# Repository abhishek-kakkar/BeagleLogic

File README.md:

===========

NEW: The BeagleLogic cape is here! To get more information please click [here]
(https://github.com/abhishek-kakkar/BeagleLogic/wiki/The-BeagleLogic-Cape).

Bootstrapped as a Google Summer of Code 2014 Project with BeagleBoard.org.

For detailed information and usage guide refer to
[the project wiki](https://github.com/abhishek-kakkar/BeagleLogic/wiki)

BeagleLogic realizes a logic analyzer on the BeagleBone / the BeagleBone Black using
the Programmable Real-Time units and matching firmware and Linux kernel modules on the
BeagleBone Black.

The software should also work on the BeagleBone White, but with limited memory support
(only 256 MB instead of 512 MB)

BeagleLogic can also be used in conjunction with the sigrok projects to capture and process
the data on the BeagleBone itself. The libsigrok bindings for BeagleLogic have been accepted
into the upstream libsigrok repository.

Directories:

* firmware: PRU Firmware
* kernel: Device Tree overlay source and kernel module source and Makefile.
**The default BeagleBone kernel v4.9.31-ti-r41 and above ship with BeagleLogic support.
You can verify it using the command** ```modinfo beaglelogic```
* server: Node.JS backend and static file server for the web interface
* cape: The cape design files (KiCAD schematic and PCB file only. Production Gerbers are available separately.)
* webapp: A minimal web client for BeagleLogic. Uses sigrok-cli internally for data
acquisition
* testapp: A simple test application that shows how to use the userspace API of BeagleLogic
and benchmarks memory copy speeds.
 
Selected binaries and archives related to the project may be downloaded from
[this link](http://goo.gl/770FTZ). Refer to the wiki for more information 
regarding the use of the archives and the binaries.

License
--------

 * **PRU firmware & Device tree overlay** : GPLv2
 * **Kernel Module**: GPLv2
 * **sigrok bindings**: GPLv3+
 * **Web interface** [/beaglelogic-server and /webapp]: MIT
 * **Cape** : CERN Open Hardware License
 * **Logo** : [Creative Commons Attribution-ShareAlike 4.0 International (CC-BY-SA-4.0)]
(http://creativecommons.org/licenses/by-sa/4.0/)

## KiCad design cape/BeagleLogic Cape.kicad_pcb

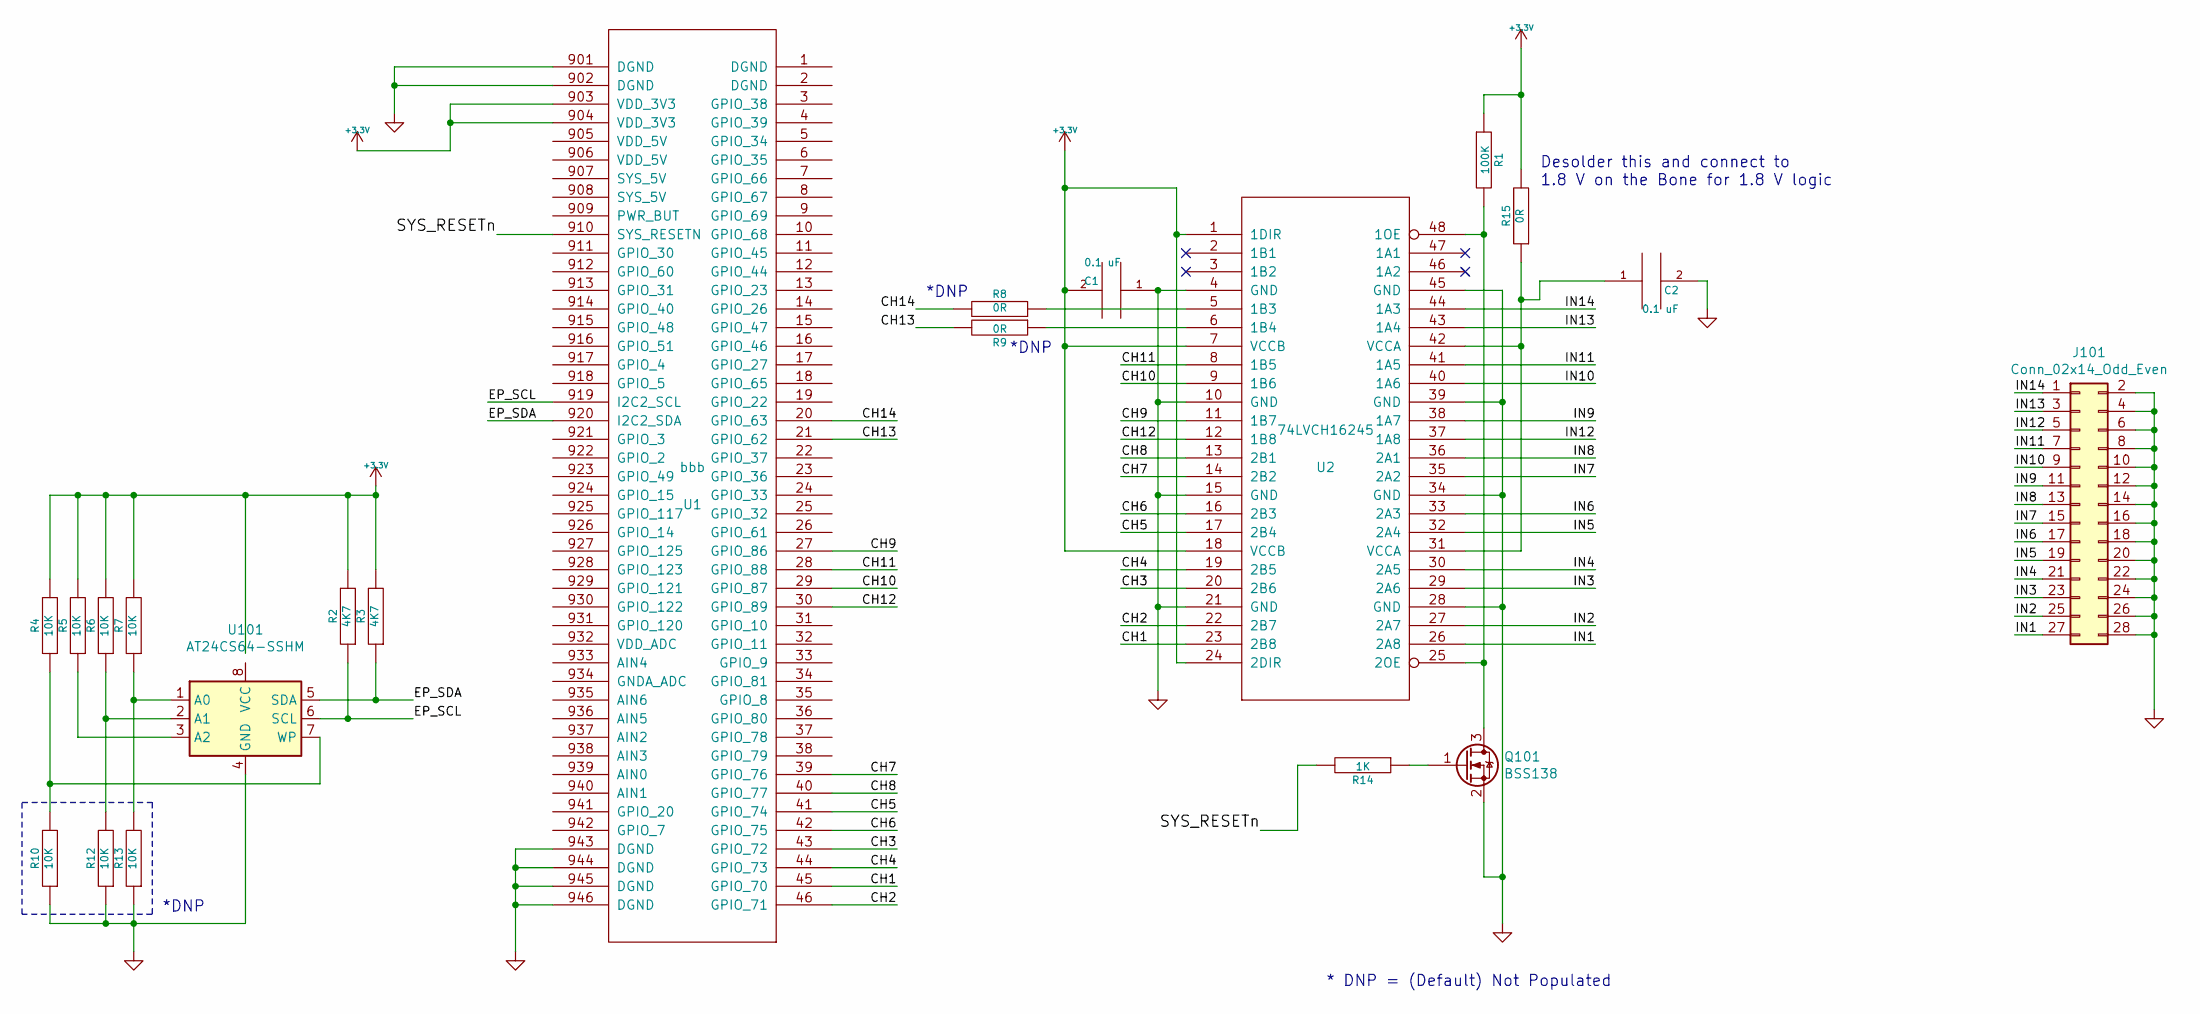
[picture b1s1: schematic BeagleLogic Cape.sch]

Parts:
C1, C2: 0.1 uF; SMD-0603
J101: Conn_02x14_Odd_Even; Pin_Header_Angled_2x14
Q101: BSS138; SOT-23_Handsoldering
R1: 100K; R_0603
R2, R3: 4K7; R_0603
R4, R5, R6, R7, R10, R12, R13: 10K; R_0603
R8, R9, R15: 0R; R_0603
R14: 1K; R_0603
U1: bbb; BBB
U2: 74LVCH16245; TSSOP-48_6.1x12.5mm_Pitch0.5mm
U101: AT24CS64-SSHM; SOIC-8-N

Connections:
+3V3: C1.2, R1.1, R2.2, R3.2, R4.2, R5.2, R6.2, R7.2, R15.2, U1.903 (VDD_3V3), U1.904 (VDD_3V3), U2.1 (1DIR), U2.7 (VCCB), U2.18 (VCCB), U2.24 (2DIR)
/CH1: U1.45 (GPIO_70), U2.23 (2B8)
/CH2: U1.46 (GPIO_71), U2.22 (2B7)
/CH3: U1.43 (GPIO_72), U2.20 (2B6)
/CH4: U1.44 (GPIO_73), U2.19 (2B5)
/CH5: U1.41 (GPIO_74), U2.17 (2B4)
/CH6: U1.42 (GPIO_75), U2.16 (2B3)
/CH7: U1.39 (GPIO_76), U2.14 (2B2)
/CH8: U1.40 (GPIO_77), U2.13 (2B1)
/CH9: U1.27 (GPIO_86), U2.11 (1B7)
/CH10: U1.29 (GPIO_87), U2.9 (1B6)
/CH11: U1.28 (GPIO_88), U2.8 (1B5)
/CH12: U1.30 (GPIO_89), U2.12 (1B8)
/CH13: R9.2, U1.21 (GPIO_62)
/CH14: R8.2, U1.20 (GPIO_63)
/EP_SCL: R2.1, U1.919 (I2C2_SCL), U101.6 (SCL)
/EP_SDA: R3.1, U1.920 (I2C2_SDA), U101.5 (SDA)
/IN1: J101.27, U2.26 (2A8)
/IN2: J101.25, U2.27 (2A7)
/IN3: J101.23, U2.29 (2A6)
/IN4: J101.21, U2.30 (2A5)
/IN5: J101.19, U2.32 (2A4)
/IN6: J101.17, U2.33 (2A3)
/IN7: J101.15, U2.35 (2A2)
/IN8: J101.13, U2.36 (2A1)
/IN9: J101.11, U2.38 (1A7)
/IN10: J101.9, U2.40 (1A6)
/IN11: J101.7, U2.41 (1A5)
/IN12: J101.5, U2.37 (1A8)
/IN13: J101.3, U2.43 (1A4)
/IN14: J101.1, U2.44 (1A3)
/SYS_RESETn: R14.2, U1.910 (SYS_RESETN)
GND: C1.1, C2.2, J101.2, J101.4, J101.6, J101.8, J101.10, J101.12, J101.14, J101.16, J101.18, J101.20, J101.22, J101.24, J101.26, J101.28, Q101.2 (S), R10.1, R12.1, R13.1, U1.901 (DGND), U1.902 (DGND), U1.943 (DGND), U1.944 (DGND), U1.945 (DGND), U1.946 (DGND), U2.4 (GND), U2.10 (GND), U2.15 (GND), U2.21 (GND), U2.28 (GND), U2.34 (GND), U2.39 (GND), U2.45 (GND), U101.4 (GND)
unnamed: C2.1, R15.1, U2.31 (VCCA), U2.42 (VCCA)
unnamed: Q101.1 (G), R14.1
unnamed: Q101.3 (D), R1.2, U2.25 (2OE), U2.48 (1OE)
unnamed: R5.1, U101.3 (A2)
unnamed: R8.1, U2.5 (1B3)
unnamed: R9.1, U2.6 (1B4)
unnamed: R4.1, R10.2, U101.7 (WP)
unnamed: R6.1, R12.2, U101.2 (A1)
unnamed: R7.1, R13.2, U101.1 (A0)

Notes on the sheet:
*DNP
* DNP = (Default) Not Populated
Desolder this and connect to 1.8 V on the Bone for 1.8 V logic

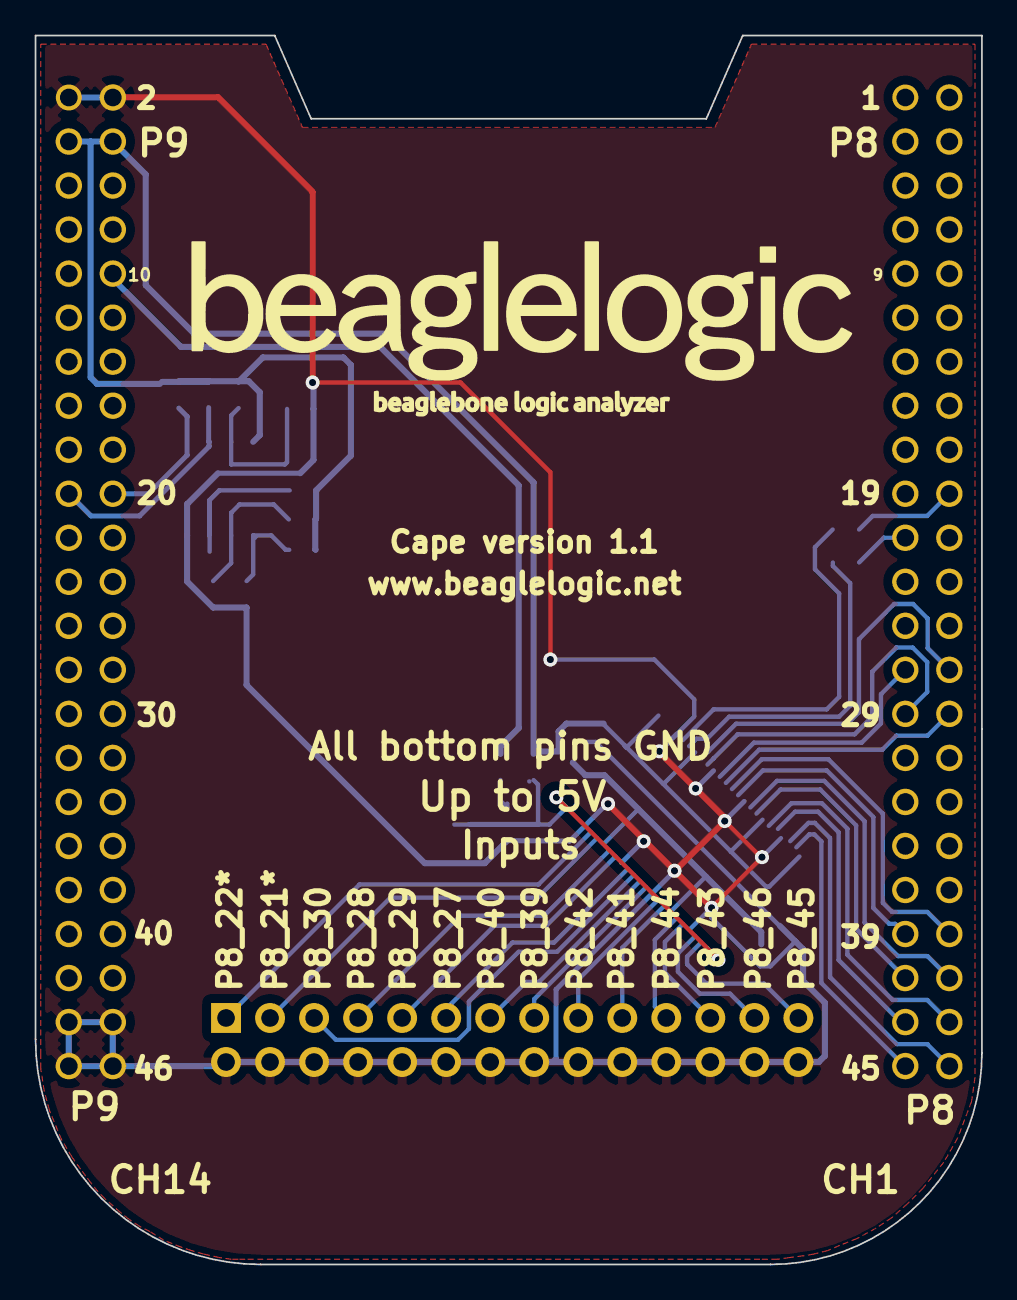
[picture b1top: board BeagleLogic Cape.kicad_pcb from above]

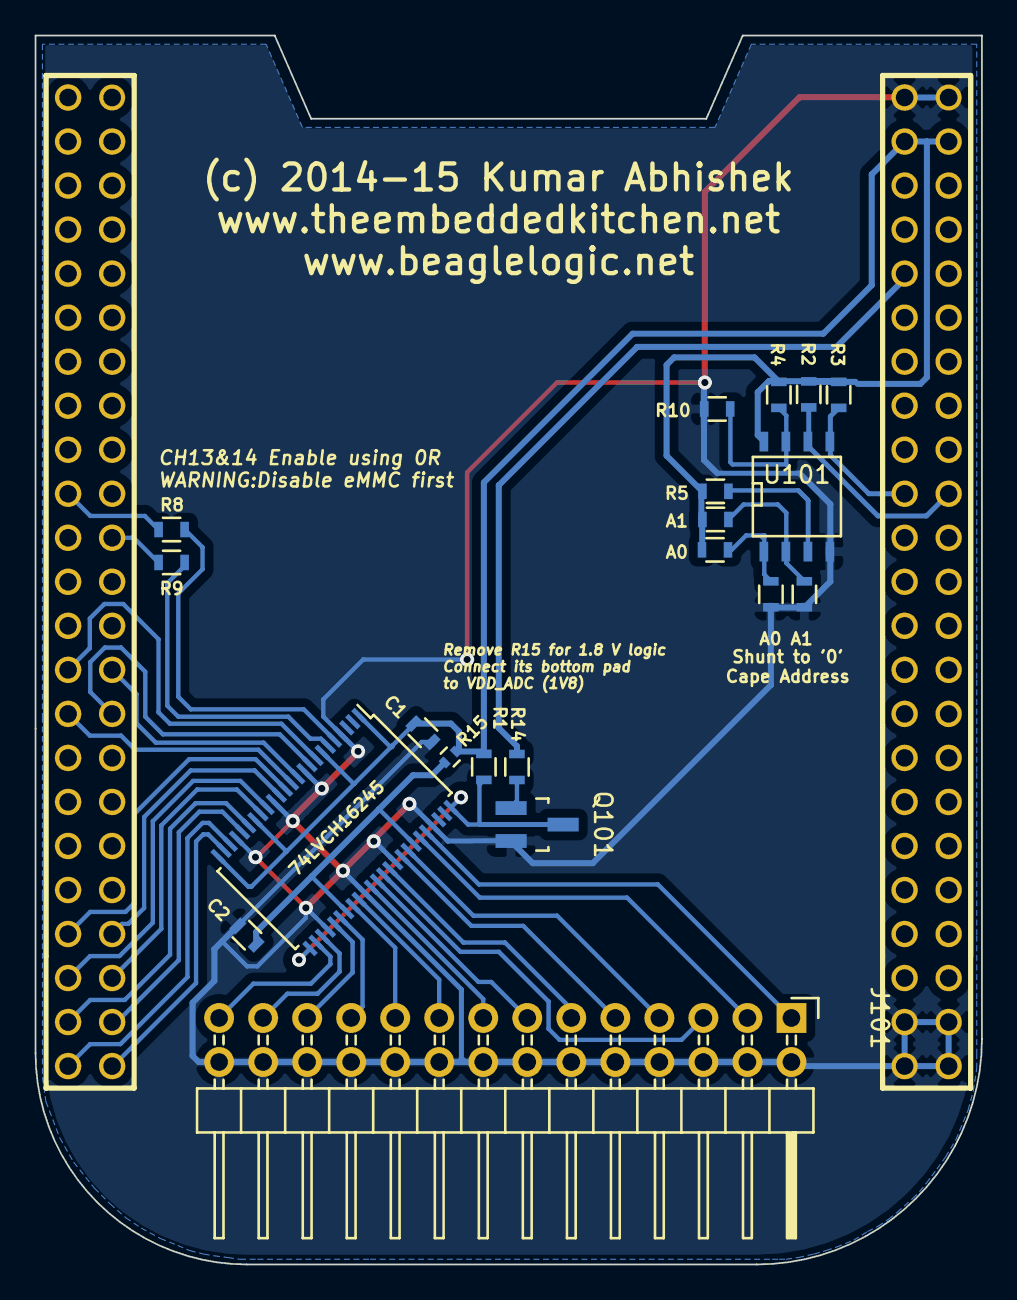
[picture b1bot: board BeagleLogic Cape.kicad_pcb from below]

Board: 2 copper layers, 54.6 x 70.9 mm, 21 parts (21 on the bottom side), 42 nets.

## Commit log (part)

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2014-05-13 .gitignore update
2014-05-13 README.md update
2014-05-20 More PRU stuff
2014-05-21 Broadside transfers working: First implementation
    Next stop: Circular transfers
2014-05-23 [pru1fw.asm]: Shift sample bank from R4-R11 to R14-R21 (possibly till R29)
2014-06-05 Add BeagleLogic device tree file and compiled overlay
2014-06-05 Add fork of pru_rproc driver as kernel module
    pru_rproc_bl.c
    Includes Matt Ranostay's lighting example
2014-06-05 Fix compile issues arising from modularization of pru_rproc
2014-06-05 [WIP] BeagleLogic PRU Firmware port to CLPRU2.0.0
    With Makefile and linker scripts.
2014-06-09 BeagleLogic kernel driver: Update path in Makefile
2014-06-09 [PRU0 FW] Port data transfer core from PASM
2014-06-09 [PRU1 FW] Shift sample capture from R13-R21 to R21-R29
2014-06-11 Use kmalloc and cache management instead of dma_alloc_coherent
2014-06-15 Kernel Module migration stage1:Cleanup beaglelogic.c
2014-06-16 Kernel module migration: Cleanup pru_rproc_bl.c
    The code in pru_rproc_bl.c is now fully independent of
    the beaglelogic module.
    Add link functions to beaglelogic module
2014-06-18 Final touches to the glue code
2014-06-20 [PRU0FW Core] Cleanup & Enable halt-on-hostrequest
    The PRU firmware now aborts sampling and resets after
    receiving an ARM->host1 interrupt
2014-06-20 [PRU1FW] Unified firmware for all sample configs
    The delay loop values are written into PRU1 registers by
    PRU0 and are used to jump to the appropriate (8-bit or
    16-bit sample) sample loop.
    Supported sample rates: (100 / n) MHz
    Sample units: 8 bits or 16-bits
2014-06-20 Kernel Driver: Add idx parameter to pru_start
    For future use, single-PRU firmware
2014-06-20 Kernel Driver: Assorted Cleanups & Fixes
    TODO:
    * Implement write overrun checks
    * Device tree parameter reads
2014-06-22 Kernel Driver: Add version information & load-time alloc unit setting
2014-06-22 Kernel Driver: Add loading initial configuration from the device tree
2014-06-22 Kernel Driver: Fix behaviour of sysfs state attribute
2014-06-22 Kernel Driver: cleanup core data structures
2014-06-22 Kernel Driver: implement overrun detection
    This allows the driver to flag a warning log & lasterror when a new
    buffer comes in before the previous one has been copied out completely.
    Also modify IRQ to prevent false buffer overrun on the last buffer
    readout.
2014-06-22 Kernel Driver: more cleanups
    Change loglevel of select messages to dev_dbg
2014-06-22 DTS: Rename to BB-BEAGLELOGIC-00A0.dts
2014-06-22 PRU Firmware: Add install-tobb target
    This copies the generated binaries to BB via SCP.
    Host may be changed using BBHOST
2014-06-23 Kernel Driver: Backport & Remove pru_rproc_bl.c
    Removed as modifications backported to pru_rproc.c
    The module is still located in the pru_rproc_bl branch
    for further modifications.
2014-06-26 Kernel Driver: Fix poll()
    Fixes infinite loop and a segfault occurring due to poll() called before
    data was actually reading from the buffer.
2014-06-26 libbeaglelogic initial commit
2014-06-26 libbeaglelogic.h: Cosmetic changes
    The syscalls have been moved to a separate file, hence this change
2014-07-01 Kernel Driver: read() ignores null pointers
2014-07-01 Kernel Driver: fix poll()
2014-07-01 libbeaglelogic: implement non-block open()
2014-07-01 testapp: add .gitignore
2014-07-01 Revert "Kernel Driver: Update buffer mapping ops in IRQ"
    This reverts commit d8f80e76722e721e56fd743be38afd088ad3df50.
2014-07-05 Kernel Module: bump version to v1.1
2014-07-29 webapp: Initial Commit
    * Built with Bootstrap v3
    * Socket.IO link
    * LZ4 and LargeLocalStorage libraries for storage of large blobs in the browser itself
2014-07-29 Add index.html for static site
2014-08-06 beaglelogic-server: Modify lz4 ver in package.json
2014-08-06 webapp: Working with server and rendering waveforms
    * Fix some whitespace as well
2014-08-09 beaglelogic-server: Remove debug functions
2014-08-09 webapp: Mark checkboxes with unique class
    To allow ease of selection with jQuery selectors
2014-08-09 webapp: Include non-minified WaveDrom
2014-08-09 webapp: Add Socket.IO presence detection
2014-08-10 webapp: Prefix local variables with 'var'
2014-08-10 webapp: Raise error and stop when no pin selected
    for capture
2014-12-28 webapp: Fix hardcoded values
2015-01-07 Add project logo under CC-BY-SA-4.0
2015-01-07 cape: Initial commit - v1.1
    Changes since v1.0 :
    * Fix errata (wrong DIR)
    * Change the board outline
2015-08-09 beaglelogic-server: Add support for > 8 channels over web interface
2015-08-09 cape: Update schematic to reflect latest KiCad dev version
2016-06-11 Announce custom firmware support for BeagleLogic.
2016-07-20 Add firmware and support for the PRUDAQ board
    Firmware put in as the first customized version of BeagleLogic's PRU1 firmware
2017-02-04 errors with structs in process thread
2017-02-05 Fixed all errors and warnings code does not run as expected more debugging is required. Most likley somthing is wrong with the process thread
2017-02-06 Fixed missing channels in tester1
2017-02-06 removed process thread. Will use main thread to read and store byte data from device file. Included new file beaglelogic_seniorDesignV2.c
2017-02-06 fixed errors inside seniorDesign.c both threads are now running
2017-02-07 Code for Arduino test simulator
    Use this code to validate the Pulse Input process and logger is functioning correctly.
2017-02-08 tested mosquito files
2017-02-08 fix to quad count
2017-02-08 fixed quadrature counter functionality
2017-02-08 daphnes code tkaes 1.4s
2017-02-08 added some more opptimaization notes
2017-02-09 made quadrature counting function inline
2017-02-10 moved every function in use from seniorDesign.c to beaglelogic_seniorDesignV2.c
2017-02-10 fixed more errors
2017-02-14 got paho to build we should use it much faster development
2017-02-17 Moved functions back into seniorDesign fixed global varibale problem
2017-02-17 implemented a .5 timer to controll mqtt thread
2017-02-20 first attempt at publish in MQTT thread
2017-02-20 got the semaphore stuff to work
2017-02-22 fixes to header file and MQTT_package
2017-02-23 fixed beaglelogic_seniorDesignV2.c
2017-02-26 major syntax issues
2017-02-26 never created struct
2017-02-26 changed switch to if
2017-02-27 Error off because we never casted to int
2017-02-27 need to change init
2017-02-27 printing out counts
2017-02-28 fixedvariables
2017-02-28 Took out some comments and added others for clarity
2017-02-28 putting this on puase do to publishing issues
2017-02-28 Need to convert counts in states to arrays
2017-02-28 compiles
2017-03-01 added j to seniordesign.c to avoid confusion
2017-03-02 replace huge block in seniorDesign.c
2017-03-02 needs fixing
2017-03-02 rising edges are counting
2017-03-02 change j
2017-03-02 timing
2017-03-02 time fixes
2017-03-16 just did some text changes
2017-05-26 Firmware: Make firmware compile under new Makefile
2017-06-04 Firmware: Add deploy targets
    On a BeagleBone, these update the firmware and reboot the PRUs.
2017-06-04 Firmware: Update PRU0 ASM function code
2017-06-04 Firmware: Remove rpmsg functionality from PRU0
2017-06-04 Kernel Driver: New device tree overlay
    This overlay contains just the beaglelogic platform device entry.
    Pinmux will be configured using cape-universal overlay.
2017-06-04 Kernel Driver: Replace ccontext structure
    Sync with PRU firmware
2017-06-04 Kernel Driver: Increment Version
2017-06-05 Kernel Driver: Add doc comment to send_cmd function
2017-06-05 Kernel Driver: Remove downcalls and replace with new command mechanism
2017-06-06 Kernel Driver: Remove typedefs from structs
    In line with Linux kernel code consensus on not to add typedefs for structs
2017-06-06 Kernel Driver: Fix incorrect sampleunit value shown
2017-06-07 Kernel Driver: Minor change to code appearance
2017-06-07 Kernel Driver: Fix spurious buffer drop warning
    The issue occurs when a running capture in continuous capture mode is
    terminated, then the wait on the last buffer read is interrupted due to
    a signal rather than being woken up from an interrupt.
    Add a check to see if the wait was interrupted in beaglelogic_f_read, if the
    wait was indeed interrupted, then return -ERESTARTSYS. This fixes the issue.
2017-06-07 Firmware: Remove syscall file
2017-06-10 Kernel Driver: Minor reorg in beaglelogic_probe code
2017-06-10 Kernel Driver: Fix waiting indefinitely in single-shot mode
    In one-shot mode BeagleLogic firmware stops automatically and state is reset to
    STATE_BL_INITIALIZED. beaglelogic_stop did not check for this condition and
    hence was waiting indefinitely after setting state to STATE_BL_REQUEST_STOP in
    one-shot mode. Adding a conditional fixes this issue.
2017-06-10 Kernel Driver: Propagate return code of beaglelogic_memalloc in sysfs and ioctl
2017-06-12 Kernel Driver: Remove old DT overlay
2017-06-12 Firmware: Modify deploy target in Makefile to not auto-reboot PRUs
    As firmware loading and unloading is now handled by the kernel driver,
    remove PRU reboot functionality.
2017-06-15 Kernel Driver: Catch-up with pru_rproc API change, fix compile error
2017-06-15 Device Tree: Rename to beaglelogic-00A0.dts
2017-06-16 Update README with new directory locations and kernel version
2017-06-22 Firmware: Change return type to fix compiler warning
2017-07-04 scripts: Add udev rule
    This udev rule allows BeagleLogic attributes to be modified by the user
    without root permissions
2017-07-04 scripts: Add BeagleLogic startup service and script
    This script initializes BeagleLogic on system startup
2017-07-04 Add install.sh script to install BeagleLogic on a blank BeagleBone system
2017-07-04 install.sh : Add install npm modules
2017-07-04 install.sh: Temporarily disable sigrok install
    ..as it is broken on Debian Stretch
2017-07-04 scripts: Add successfully loaded message to startup script
2017-07-04 install.sh: Add command to just update uEnv.txt
2017-07-05 bone_pwm_P9_31-00A0.dts: add legacy overlay and update Makefile
    * note this does not yet produce a usable pwm_test_P9_31 device with files
    to set duty cycle and period
2017-07-12 scripts: Switch loading overlays from config-pin to slots
2017-07-19 tcp-server: Initial Commit
    Add draft TCP server written in node.js for sigrok clients to connect to
2017-07-21 installer: Add --upgrade switch
    The --upgrade switch upgrades an existing BeagleLogic installation.
    It disables creating the beaglelogic group and the uboot updation which
    is done by default during installation.
2017-07-21 docs: Add "no-installation-required" to BeagleLogic system image
2017-07-21 docs: Add "Differences between BeagleLogic on 4.9 vs 3.8 kernels"
2017-07-21 docs: Expand index.rst with additional text from the wiki
2017-10-07 beaglelogic-startup.sh: Increase buffer to 128MiB
2017-10-07 TCP Server: Suppress errors, also log received commands
    And fixes to EPIPE and ECONNRESET on incomplete reads.
2017-10-07 scripts: Add support for BeagleLogic standalone board
    The board has an on board logic buffer that needs to be enabled
    at startup via a GPIO. There is also switchable logic level thresholds
    between 1.8V and 3.3V via a GPIO and that control is exposed through
    another GPIO. Add support to set both the GPIOs and also gate config-pin
    (as it is not required as pinmuxing is handled in the device tree)
2017-10-08 tcp-server: Rewrite in Go for less memory footprint
    The original tcp-server written in node.js was occupying too much
    memory, hence replace it with an implementation in Go.
2017-10-08 install.sh: Add installation of Go and compilation of tcp server
2017-10-13 webapp: Update branding and help text to BeagleLogic standalone
2017-10-20 docs: Add sysfs attributes page
2017-10-20 docs: Fix BeagleLogic standalone link
2018-12-08 make the cape pass electrical rules check
2019-10-22 build(deps): bump express from 3.2.6 to 4.17.1 in /server
    Bumps [express](https://github.com/expressjs/express) from 3.2.6 to 4.17.1.
    - [Release notes](https://github.com/expressjs/express/releases)
    - [Changelog](https://github.com/expressjs/express/blob/master/History.md)
    - [Commits](https://github.com/expressjs/express/compare/3.2.6...4.17.1)
2020-07-05 kernel: Change var name to fix #34
2020-07-05 kernel: Now builds on 5.4-ti branch

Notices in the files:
cape/BeagleLogic Cape.kicad_pcb:
(c) 2014-15 Kumar Abhishek
